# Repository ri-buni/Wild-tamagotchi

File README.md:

# Wild-tamagotchi
Two pet tamagotchi, they have their own states and you can switch from one to another. Button 1 is for turning left, Button 2 is for turning right, Button 3 is for action, Button 4 is for switching bunnies and double tap on Button 4 is for turning on and off.

# PCB made in KiCad

Schematic

PCB

# CAD made in Fusion360

# Firmware 

Made with Claude Code, but the character itself and drawinng were made by me.

# BOM

| Item | Description | Qty | Unit Price | Line Total | Source |
|---|---|---|---|---|---|
| PCB | Custom 2-layer PCB | 1 | $10.00 | $10.00 | [JLCPCB](https://jlcpcb.com/) |
| LiPo battery | 500mAh 3.7V | 1 | $5.10 | $5.10 | [AliExpress](https://aliexpress.ru/item/1005006462526013.html?sku_id=12000037283411655) |
| TP4056 | Li-ion charger module | 1 | $0.50 | $0.50 | [AliExpress](https://aliexpress.ru/item/32453058256.html?sku_id=12000052763412620) |
| Buttons | 6x6 tactile push buttons | 1 | $0.80 | $0.80 | [AliExpress](https://aliexpress.ru/item/1005007623070623.html?sku_id=12000041542638534) |
| ESP32 DevKitC | MCU dev board | 1 | $4.00 | $4.00 | [AliExpress](https://aliexpress.ru/item/1005006737960797.html?sku_id=12000038137904831) |
| 2.42" OLED | 128x64 SSD1309, I2C/SPI | 1 | $12.00 | $12.00 | [AliExpress](https://aliexpress.ru/item/1005008770450001.html?sku_id=12000046598711076) |
| Shipping | AliExpress shipping | 1 | $2.00 | $2.00 | AliExpress |
| **GRAND TOTAL** |  |  |  | **$34.40** |  |

So your estimated price would be 30-35$

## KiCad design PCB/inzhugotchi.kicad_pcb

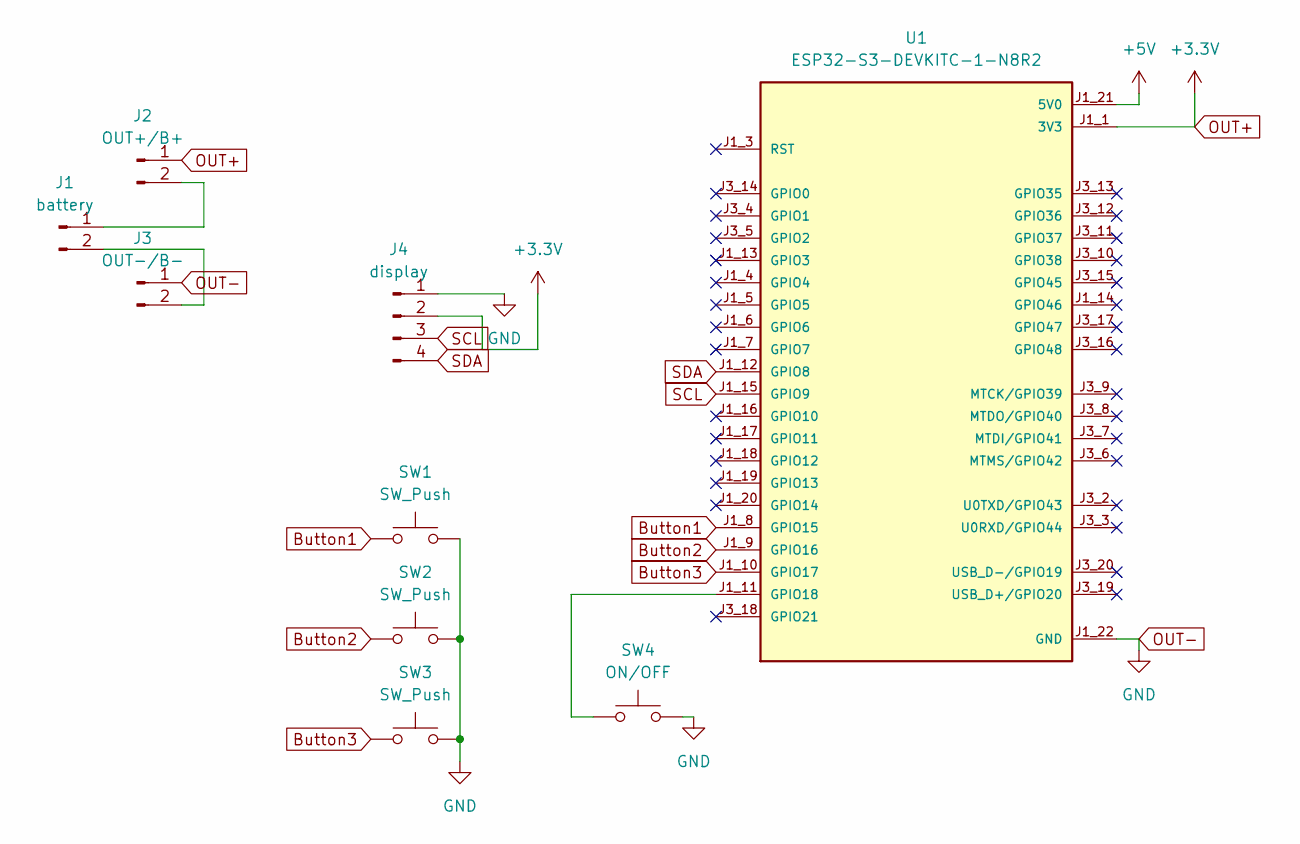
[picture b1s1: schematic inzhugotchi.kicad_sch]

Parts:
J1: battery; PinHeader_1x02_P2.54mm_Vertical
J2: OUT+/B+; PinHeader_1x02_P2.54mm_Vertical
J3: OUT-/B-; PinHeader_1x02_P2.54mm_Vertical
J4: display; PinSocket_1x04_P2.54mm_Vertical
SW1, SW2, SW3: SW_Push; SW_PUSH_6mm
SW4: ON/OFF; SW_PUSH_6mm
U1: ESP32-S3-DEVKITC-1-N8R2; XCVR_ESP32-S3-DEVKITC-1-N8R2; PARTREV V1

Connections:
+5V: U1.J1_21 (5V0)
Button1: SW1.1, U1.J1_8 (GPIO15)
Button2: SW2.1, U1.J1_9 (GPIO16)
Button3: SW3.1, U1.J1_10 (GPIO17)
unnamed: J1.1, J2.2
unnamed: J1.2, J3.2
unnamed: SW4.1, U1.J1_11 (GPIO18)
OUT+: J2.1, J4.2, U1.J1_1 (3V3), U1.J1_2 (3V3)
OUT-: J3.1, J4.1, SW1.2, SW2.2, SW3.2, SW4.2, U1.J1_22 (GND), U1.J3_1 (GND), U1.J3_21 (GND), U1.J3_22 (GND)
SCL: J4.3, U1.J1_15 (GPIO9)
SDA: J4.4, U1.J1_12 (GPIO8)

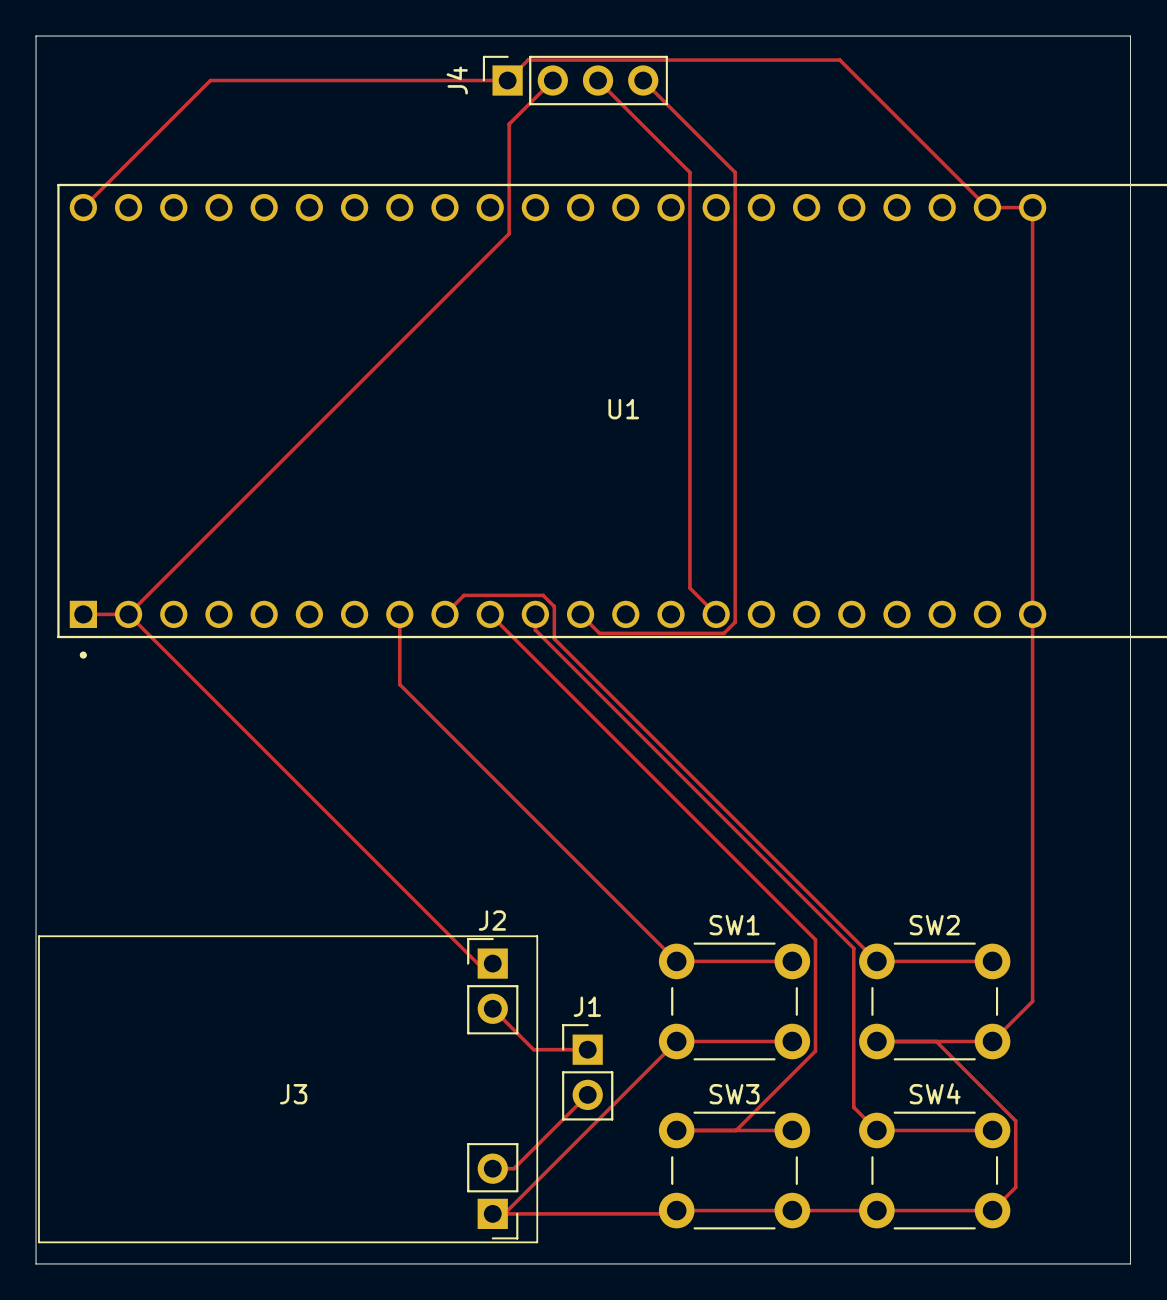
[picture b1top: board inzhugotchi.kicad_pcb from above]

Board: 2 copper layers, 61.5 x 69.0 mm, 9 parts (0 on the bottom side), 10 nets.

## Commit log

2026-05-24 Correct capitalization in project description
2026-05-26 Create s
2026-05-26 Create a
2026-05-27 Rename project from inzhugotchi to wildgotchi
2026-06-12 Rename wildgotchi.zip to gerbers.zip
2026-06-13 Create ds
